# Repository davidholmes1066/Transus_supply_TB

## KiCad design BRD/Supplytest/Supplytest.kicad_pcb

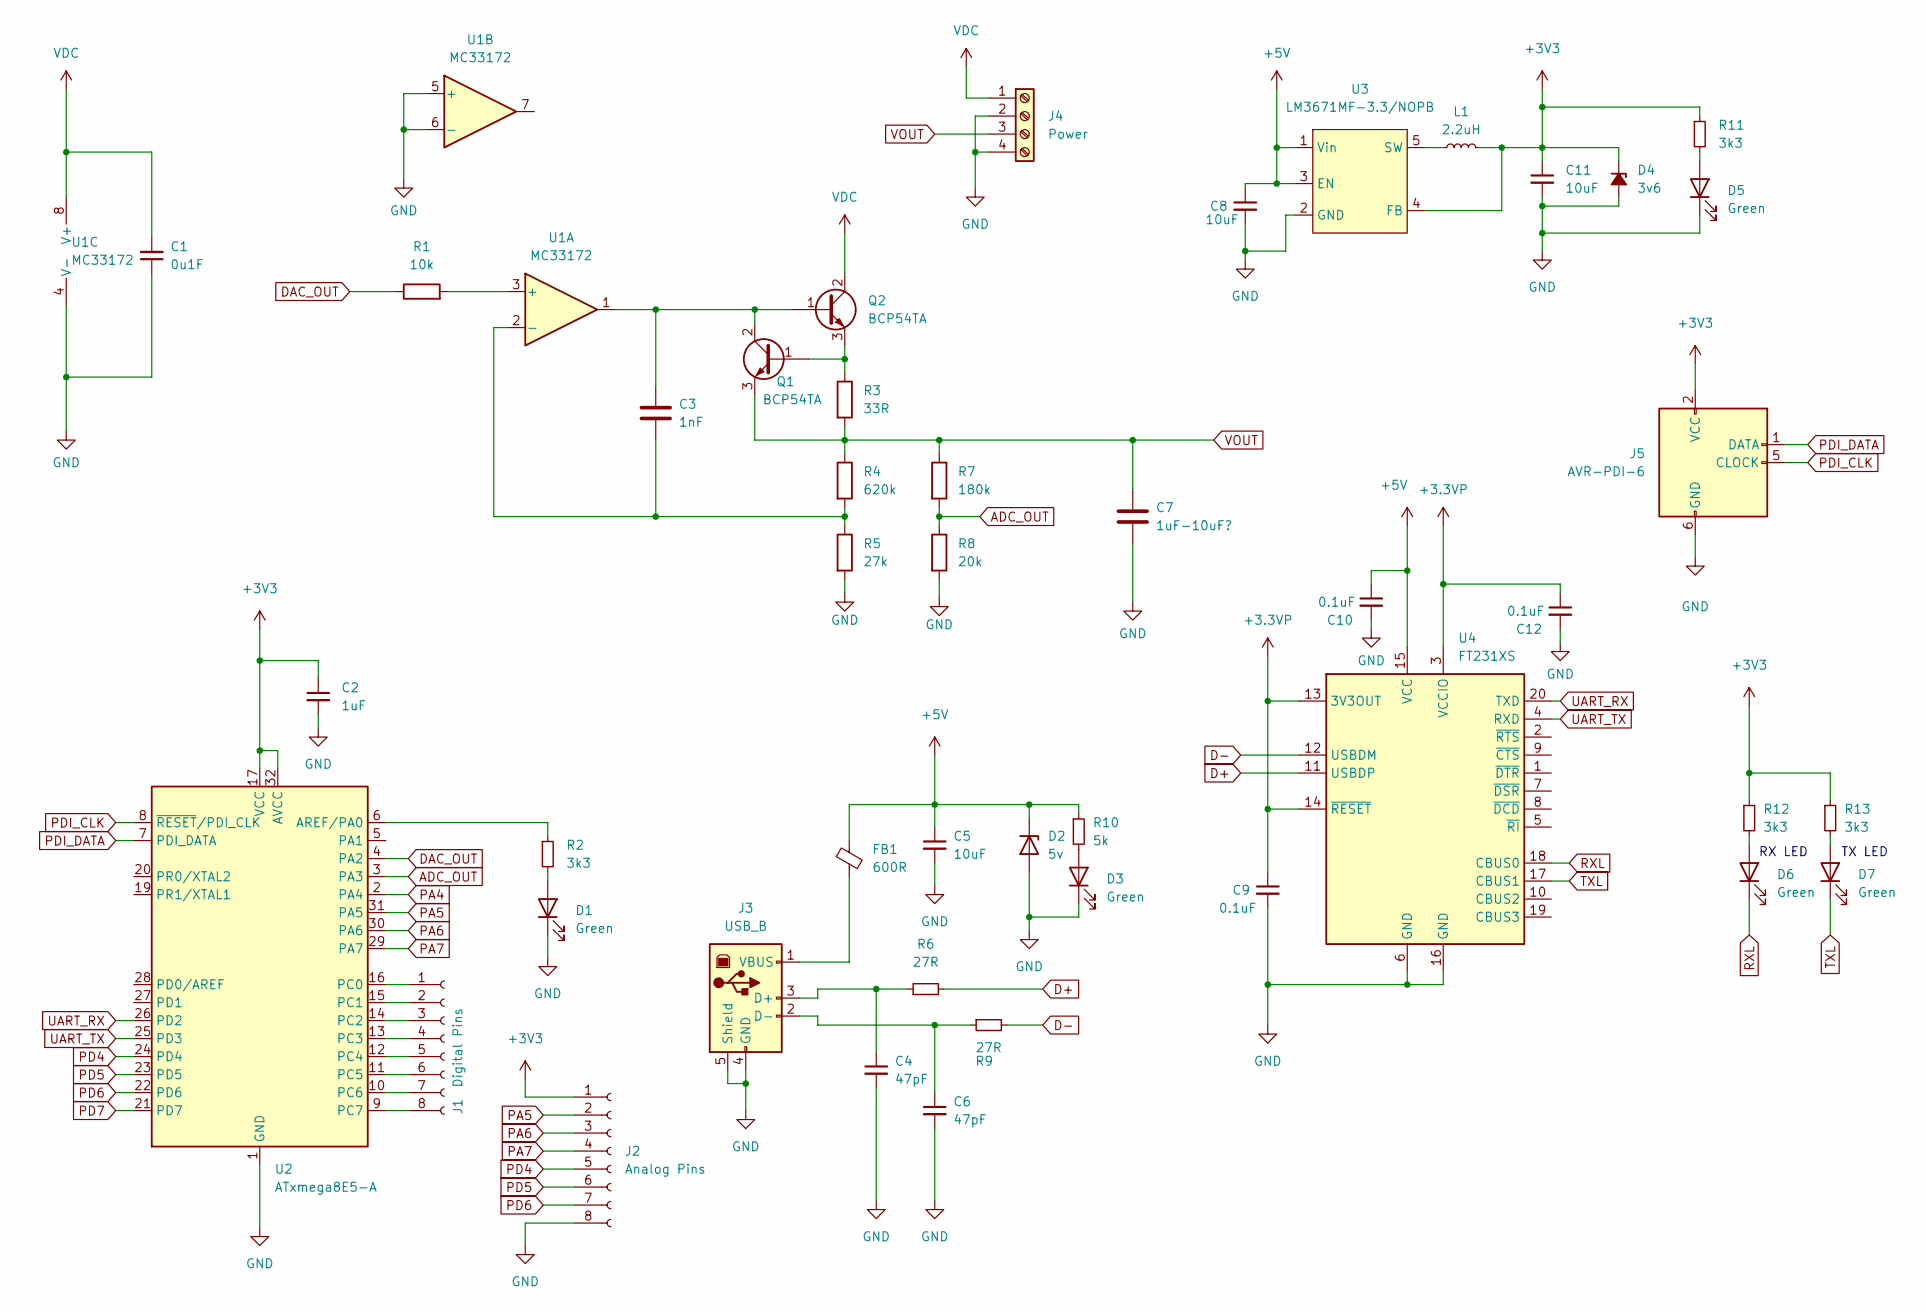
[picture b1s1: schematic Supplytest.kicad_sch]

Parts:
C1: 0u1F; C_0805_2012Metric_Pad1.18x1.45mm_HandSolder
C2: 1uF; C_0805_2012Metric_Pad1.18x1.45mm_HandSolder
C3: 1nF; C_0805_2012Metric_Pad1.18x1.45mm_HandSolder
C4, C6: 47pF; C_0805_2012Metric_Pad1.18x1.45mm_HandSolder
C5, C8, C11: 10uF; C_0805_2012Metric_Pad1.18x1.45mm_HandSolder
C7: 1uF-10uF?; C_0805_2012Metric_Pad1.18x1.45mm_HandSolder; FARNELL 2611936
C9, C10, C12: 0.1uF; C_0805_2012Metric_Pad1.18x1.45mm_HandSolder
D1, D3, D5, D6, D7: Green; LED_0402_1005Metric_Pad0.77x0.64mm_HandSolder; Farnell 2507544
D2: 5v; D_SOD-123
D4: 3v6; BZX84C3V6; Farnell 1902466
FB1: 600R; C_0805_2012Metric_Pad1.18x1.45mm_HandSolder; Farnell 1838838
J1: Digital Pins; PinHeader_1x08_P2.54mm_Vertical
J2: Analog Pins; PinHeader_1x08_P2.54mm_Vertical
J3: USB_B; Farnell 1860556
J4: Power; Screwterminal_3mm81_4pos
J5: AVR-PDI-6; TagConnect_Avr
L1: 2.2uH; 0805_PInductor; Farnell 3865051
Q1, Q2: BCP54TA; SOT-223-3_TabPin2; FARNELL 3943121
R1: 10k; R_0805_2012Metric_Pad1.20x1.40mm_HandSolder; FARNELL 2447640
R2, R11, R12, R13: 3k3; R_0805_2012Metric_Pad1.20x1.40mm_HandSolder
R3: 33R; R_0805_2012Metric_Pad1.20x1.40mm_HandSolder; FARNELL 2447640
R4: 620k; R_0805_2012Metric_Pad1.20x1.40mm_HandSolder
R5: 27k; R_0805_2012Metric_Pad1.20x1.40mm_HandSolder
R6, R9: 27R; R_0805_2012Metric_Pad1.20x1.40mm_HandSolder
R7: 180k; R_0805_2012Metric_Pad1.20x1.40mm_HandSolder
R8: 20k; R_0805_2012Metric_Pad1.20x1.40mm_HandSolder
R10: 5k; R_0805_2012Metric_Pad1.20x1.40mm_HandSolder
U1: MC33172; SO-8_3.9x4.9mm_P1.27mm
U2: ATxmega8E5-A; TQFP-32_7x7mm_P0.8mm
U3: LM3671MF-3.3/NOPB; SOT-23-5_HandSoldering; Farnell 3008192
U4: FT231XS; SSOP-20_3.9x8.7mm_P0.635mm

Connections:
+3.3VP: C9.1, C12.1, U4.3 (VCCIO), U4.13 (3V3OUT), U4.14 (~RESET)
+3V3: C2.1, C11.1, D4.1 (K), J2.1, J5.2 (VCC), L1.2, R11.1, R12.1, R13.1, U2.17 (VCC), U2.32 (AVCC), U3.4 (FB)
+5V: C5.1, C8.1, C10.1, D2.1 (K), FB1.1, R10.1, U3.1 (Vin), U3.3 (EN), U4.15 (VCC)
ADC_OUT: R7.2, R8.1, U2.3 (PA3)
D+: R6.2, U4.11 (USBDP)
D-: R9.2, U4.12 (USBDM)
DAC_OUT: R1.1, U2.4 (PA2)
GND: C1.1, C2.2, C4.2, C5.2, C6.2, C7.2, C8.2, C9.2, C10.2, C11.2, C12.2, D1.1 (K), D2.2 (A), D3.1 (K), D4.2 (A), D5.1 (K), J2.8, J3.4 (GND), J3.5 (Shield), J4.2, J4.4, J5.6 (GND), R5.2, R8.2, U1.4 (V-), U1.5 (+), U1.6 (-), U2.1 (GND), U2.18 (GND), U3.2 (GND), U4.6 (GND), U4.16 (GND)
unnamed: C3.1, Q1.2 (C), Q1.4 (C), Q2.1 (B), U1.1
unnamed: C3.2, R4.2, R5.1, U1.2 (-)
unnamed: C4.1, J3.3 (D+), R6.1
unnamed: C6.1, J3.2 (D-), R9.1
unnamed: D1.2 (A), R2.2
unnamed: D3.2 (A), R10.2
unnamed: D5.2 (A), R11.2
unnamed: D6.2 (A), R12.2
unnamed: D7.2 (A), R13.2
unnamed: FB1.2, J3.1 (VBUS)
unnamed: J1.1, U2.16 (PC0)
unnamed: J1.2, U2.15 (PC1)
unnamed: J1.3, U2.14 (PC2)
unnamed: J1.4, U2.13 (PC3)
unnamed: J1.5, U2.12 (PC4)
unnamed: J1.6, U2.11 (PC5)
unnamed: J1.7, U2.10 (PC6)
unnamed: J1.8, U2.9 (PC7)
unnamed: L1.1, U3.5 (SW)
unnamed: Q1.1 (B), Q2.3 (E), R3.1
unnamed: R1.2, U1.3 (+)
unnamed: R2.1, U2.6 (AREF/PA0)
PA4: U2.2 (PA4)
PA5: J2.2, U2.31 (PA5)
PA6: J2.3, U2.30 (PA6)
PA7: J2.4, U2.29 (PA7)
PD4: J2.5, U2.24 (PD4)
PD5: J2.6, U2.23 (PD5)
PD6: J2.7, U2.22 (PD6)
PD7: U2.21 (PD7)
PDI_CLK: J5.5 (CLOCK), U2.8 (~RESET/PDI_CLK)
PDI_DATA: J5.1 (DATA), U2.7 (PDI_DATA)
RXL: D6.1 (K), U4.18 (CBUS0)
TXL: D7.1 (K), U4.17 (CBUS1)
UART_RX: U2.26 (PD2), U4.20 (TXD)
UART_TX: U2.25 (PD3), U4.4 (RXD)
VDC: C1.2, J4.1, Q2.2 (C), Q2.4 (C), U1.8 (V+)
VOUT: C7.1, J4.3, Q1.3 (E), R3.2, R4.1, R7.1

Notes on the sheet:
TX LED
RX LED

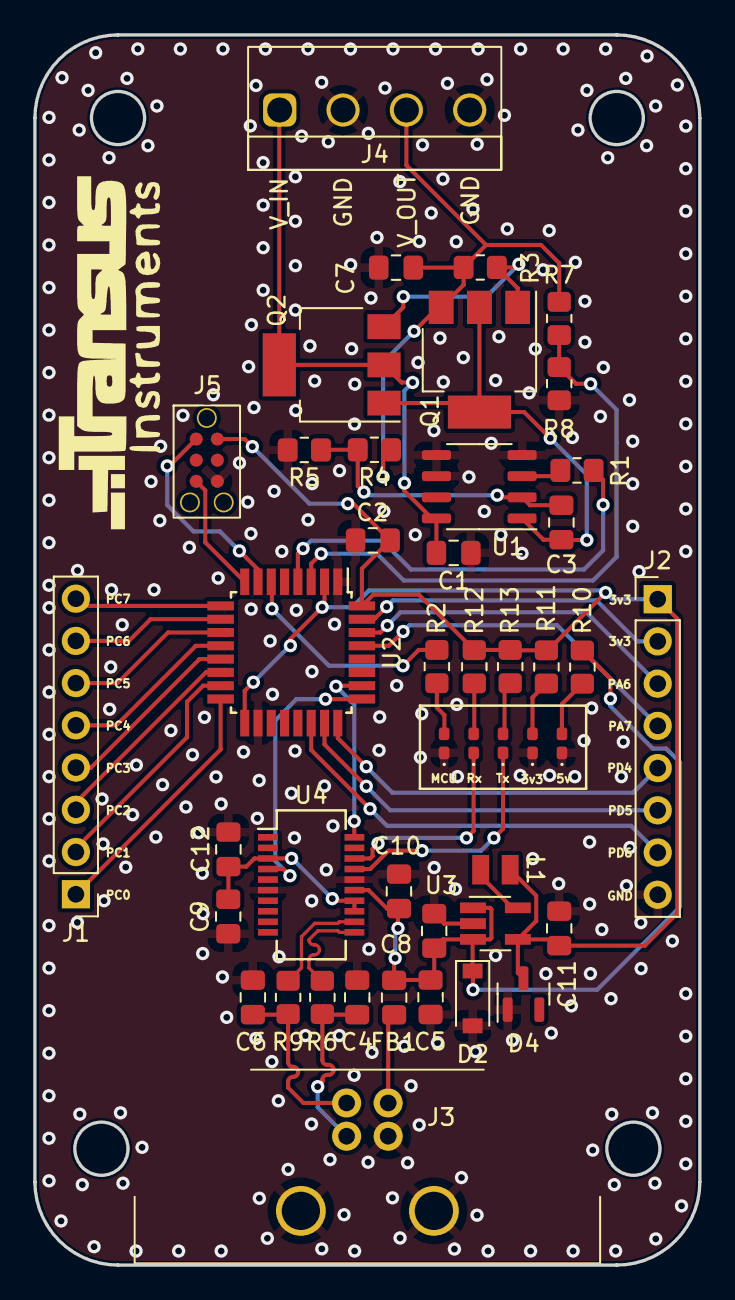
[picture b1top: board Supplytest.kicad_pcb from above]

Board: 2 copper layers, 40.0 x 74.0 mm, 45 parts (0 on the bottom side), 44 nets.

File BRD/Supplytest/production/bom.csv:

Designator,Footprint,Quantity,Value,LCSC Part #
C1,C_0805_2012Metric_Pad1.18x1.45mm_HandSolder,1,0u1F,
"C10, C12, C9",C_0805_2012Metric_Pad1.18x1.45mm_HandSolder,3,0.1uF,
"C11, C5, C8",C_0805_2012Metric_Pad1.18x1.45mm_HandSolder,3,10uF,
C2,C_0805_2012Metric_Pad1.18x1.45mm_HandSolder,1,1uF,
C3,C_0805_2012Metric_Pad1.18x1.45mm_HandSolder,1,1nF,
"C4, C6",C_0805_2012Metric_Pad1.18x1.45mm_HandSolder,2,47pF,
C7,C_0805_2012Metric_Pad1.18x1.45mm_HandSolder,1,1uF-10uF?,
"D1, D3, D5, D6, D7",LED_0402_1005Metric_Pad0.77x0.64mm_HandSolder,5,Green,
D2,D_SOD-123,1,5v,
D4,BZX84C3V6,1,3v6,
FB1,C_0805_2012Metric_Pad1.18x1.45mm_HandSolder,1,600R,
J1,PinHeader_1x08_P2.54mm_Vertical,1,Digital Pins,
J2,PinHeader_1x08_P2.54mm_Vertical,1,Analog Pins,
J3,USB_B,1,USB_B,
J4,Screwterminal_3mm81_4pos,1,Power,
J5,TagConnect_Avr,1,AVR-PDI-6,
L1,0805_PInductor,1,2.2uH,
"Q1, Q2",SOT-223-3_TabPin2,2,BCP54TA,
R1,R_0805_2012Metric_Pad1.20x1.40mm_HandSolder,1,10k,
R10,R_0805_2012Metric_Pad1.20x1.40mm_HandSolder,1,5k,
"R11, R12, R13, R2",R_0805_2012Metric_Pad1.20x1.40mm_HandSolder,4,3k3,
R3,R_0805_2012Metric_Pad1.20x1.40mm_HandSolder,1,33R,
R4,R_0805_2012Metric_Pad1.20x1.40mm_HandSolder,1,620k,
R5,R_0805_2012Metric_Pad1.20x1.40mm_HandSolder,1,27k,
"R6, R9",R_0805_2012Metric_Pad1.20x1.40mm_HandSolder,2,27R,
R7,R_0805_2012Metric_Pad1.20x1.40mm_HandSolder,1,180k,
R8,R_0805_2012Metric_Pad1.20x1.40mm_HandSolder,1,20k,
U1,SO-8_3.9x4.9mm_P1.27mm,1,MC33172,
U2,TQFP-32_7x7mm_P0.8mm,1,ATxmega8E5-A,
U3,SOT-23-5_HandSoldering,1,LM3671MF-3.3/NOPB,
U4,SSOP-20_3.9x8.7mm_P0.635mm,1,FT231XS,

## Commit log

2023-03-07 Added BRD file
2023-03-07 Added embedded software for xmega8e5
    The software needs testing and callibrating, also still need to add matlab application
